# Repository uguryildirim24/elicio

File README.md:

# Elicio

Elicio is an unfinished ear-muscle EMG earpiece that is intended to turn a deliberate contraction into a gated event before an AI acts.

Rolf chose a discreet physical input rather than an always-active command channel. The sensor should propose an event. Policy should decide whether that event can act. Sensing, permission and execution remain separate.

```text
ear-muscle EMG -> decoder -> (symbol, confidence, timestamp) -> policy -> action
```

**The board is not finished, has not been ordered and is unmeasured.** No physical earpiece, real ear-muscle recording or end-to-end biological action has been validated. The runnable demonstrations use synthetic input. Only a harmless local file action is real. No AI execution adapter is implemented.

## What exists

| Part | Files and present evidence |
| --- | --- |
| Flex board | [KiCad schematic](hardware/board/elicio-v4.kicad_sch), [routed PCB](hardware/board/elicio-v4.kicad_pcb), project rules and generation/routing scripts. Design files are not manufacturing approval. |
| Scripted shell | [Selected snap-shell exports](docs/fab/cad/v4-snap/) include STEP, STL, 3MF and a nominal-check manifest. No print, fit or retention result. |
| Firmware | [Arduino stream firmware](firmware/elicio_stream/elicio_stream.ino) and C sources for ADS1292 acquisition, binary BLE frames and undervoltage handling. The product Arduino variant is missing. |
| Receiver | Binary frame decoding, dropout/loss records and session files. Committed synthetic transport fixtures run without a radio. |
| Action gate | Confidence policy, confirmation state, intent/result auditing and an atomic local marker write. Other action names are console simulations. |
| Research pipeline | Public forearm sEMG preparation and cross-session evaluation code. No result CSVs, checkpoints or measured accuracy reports are bundled. |

The snap manifest records **106 passing nominal geometry checks**. These cover simplified board courtyards, a folded-flap envelope, seated overlap, key clearance and opposing tolerance offsets. They do not prove printed fit, latch fatigue, component loads, electrical safety or RF range. The nominal body is 18 mm wide and 8.1 mm thick, not the complete hook bounding box. See [shell limits](docs/fab/shell-v4.md) and [board blockers](docs/fab/board-v4-design.md).

## Run from a clean clone

Run these commands from the repository root on macOS or Linux. Use Python **3.11 or newer**. The base install requires NumPy. No credentials or hardware are needed for the demos.

```bash
python3 --version
python3 -m venv .venv
.venv/bin/python -m pip install -e .
.venv/bin/elicio demo --state-dir .elicio-demo
.venv/bin/elicio replay-demo --state-dir .elicio-replay-demo
```

Each demo must exit 0 and print `"verified": true`. It writes a marker under `actions/` and linked `intent` and `result` records in `audit.jsonl` inside its ignored state directory. The replay fixture is seeded synthetic data, not an EMG recording or a hardware test.

### Binary receiver without hardware

```bash
.venv/bin/elicio receive --simulate tests/fixtures/receiver_v2/normal.json \
    --out recordings/synthetic-session
.venv/bin/elicio receive-check recordings/synthetic-session
```

`receive` writes `samples.npz`, `sidecar.json` and `meta.json`. `receive-check` reports acquisition statistics and criterion status; the normal fixture exits 0 with `"ok": true`. Its gesture criteria are `not_scored`, not passed. This is transport validation, not gesture decoding or a connection to the action gate.

The intended radio path uses binary frame-v2 messages over Nordic UART Service, not ASCII serial samples. Live reception requires the optional BLE dependency and future functioning hardware:

```bash
.venv/bin/python -m pip install -e '.[ble]'
.venv/bin/elicio receive --device ELICIO --seconds 10 --out recordings/bench-session
.venv/bin/elicio receive-check recordings/bench-session
```

The live commands are not usable or validated with this unfinished board. The firmware deliberately rejects a Feather pin variant. See [firmware limits](docs/fab/firmware-v2.md), [frame format](docs/fab/frame-v2.md) and [receiver contract](docs/fab/receiver-v2.md).

The separate `scope`, `capture` and `replay-recording` tools accept one ASCII sample per line from a file, stdin or an already configured serial device. They are bench utilities, not the binary BLE path. Store captures under ignored `recordings/`, for example `--out recordings/session.json`. Run `elicio capture --help` for the sample-rate, offset and gain arguments.

### Existing tests

```bash
.venv/bin/python -m unittest discover -s tests -v
```

The scope review ran the base install, both synthetic action demos and the normal receiver fixture in the worktree with Python 3.13.15. They exited 0. Both demos reported `verified: true`; the receiver check reported `ok: true` with gesture criteria unscored.

The full existing suite was attempted but stopped at a 180-second command limit while setting up the restored packing checks. A historical document wording assertion failed before that point. Its expected reference wording was restored, and that existing test passed when rerun alone. The documented `bte_fit_shell.py --checks-only` reference check and `elicio capture --help` also passed. No complete suite pass is claimed. The original tests and historical-byte comparisons remain unchanged. No tests or CI were added.

Optional dependency groups are `research`, `ble`, `cad` and `sheets`. Install an extra with, for example, `.venv/bin/python -m pip install -e '.[cad]'`. Native C checks use a compiler when available. KiCad/pcbnew, firmware tooling, Blender or SceneKit are separate toolchains. Optional CAD exports, rendering, KiCad release validation, firmware flashing and live acquisition were not rerun during the scope review. Research downloads and training were skipped as substantial workloads.

## Research and local data

The research package fetches public PhysioNet/WFDB GRABMyo records. It studies forearm gestures, not auricular decoding. From the repository root:

```bash
.venv/bin/python -m pip install -e '.[research]'
.venv/bin/elicio-emg prepare --subjects 1 2 3 --out-dir results
.venv/bin/elicio-emg train --data-dir results --subjects 1 2 3 \
    --epochs 20 --out results/train_results.csv
.venv/bin/elicio-emg evaluate --data-dir results --subjects 1 2 3 \
    --epochs 20 --out results/six_best_rest.csv
```

These are download and training workloads, not quick demos. They were not rerun during cleanup. Training is not fully seeded. Evaluation uses separate recording sessions and a leakage guard. Earlier imported accuracy summaries lack supporting result artifacts here and are not claimed as repository results. See the [pipeline instructions](src/elicio/pipeline/README.md) and [provenance limits](docs/RESEARCH_PROVENANCE.md).

Keep raw recordings in `recordings/`, research outputs in `results/`, anatomy parameters in `measurements/` and generated CAD/release output in `.reports/`. These directories, environments, checkpoints, secrets and runtime state are ignored. Tracked binary fixtures are synthetic. No completed personal ear measurements or purchase records are included. Do not put delivery addresses, checkout details or credentials in public examples.

## Limits and next steps

- Confidence thresholds are policy settings, not calibrated biological probabilities.
- The timed `jaw_clench` confirmation rule checks symbols, confidence and timestamps. The event tuple cannot prove that command and confirmation came from independent muscle groups. That is an unvalidated upstream requirement.
- Intent audit failure blocks execution. A result-audit failure after execution is reported without hiding the completed action.
- There is no trained ear-muscle decoder, real signal-to-action result or AI execution adapter.
- The circuit, cell, charging protection, RF keep-out, programming path and manufacturing acceptance remain open. CAD and a clean DRC claim cannot establish on-body safety.
- This is not a medical device or a finished wearable. Do not wear or charge unvalidated electronics on a body.

Next: resolve electrical and fabrication blockers, implement the product firmware variant, validate passive printed fit and repeated latch retention, then record a real signal and demonstrate one harmless audited action. See [design status](docs/EARPIECE_DESIGN.md) and [open gates](docs/fab/open-questions.md).

## Project layout

| Path | Purpose |
| --- | --- |
| `src/elicio/harness/` | Events, policy, adapters and audit |
| `src/elicio/signal/` | Synthetic replay, detection and ASCII capture |
| `src/elicio/frame_v2.py`, `receiver_v2.py` | Binary BLE transport and session reception |
| `src/elicio/pipeline/` | Public-data research pipeline |
| `hardware/board/` | KiCad sources, custom footprints and board scripts |
| `firmware/` | Acquisition, framing and power-state sources |
| `scripts/cad/`, `scripts/sheets/` | Parametric CAD, previews and reference templates |
| `docs/fab/cad/v4-snap/` | Selected shell candidate and nominal evidence |
| `tests/` | Existing unit checks and synthetic transport fixtures |
| `docs/` | Design limits, provenance and engineering references |

Older v1/v2 geometry, packing tables, layout searches, board-edit scripts and their existing checks remain. They are reference inputs and development tools, not active ordering instructions. `placement.py` still supports `--packing-doc`, `--layout-v2` and `--layout-v2c`. Some older readers use pinned Git revisions. They are not independent of repository history, and history scrubbing can invalidate those references. The technical L1 to L8 source surveys remain with historical notices. The [reference index](docs/fab/references.md) lists key public sources. Task and review dialogue is omitted.

The rejected M1.6 closure remains as diagnostic code and evidence in `docs/fab/cad/v4-m16/`. It is not suitable for printing. The snap candidate is still untested physically. Private agent diaries, personal parameter scaffolding and superseded shopping sheets were removed. Historical budgets are estimates, not quotes or personal spending statements.

## How this was built

AI coding agents did much of the research migration, harness and receiver implementation, firmware, CAD and board work under Rolf's direction. Rolf set the physical-gating goal, chose the earpiece form, titanium contacts, limited final assembly and off-ear-only charging, and reviewed design previews. The checks reported here are automated software and nominal geometry checks. Agent-written engineering claims are not independent electrical review or physical measurements. No hardware result has been measured.

## License and citation

Original project code, hardware design files and documentation are offered under [MIT](LICENSE). The bundled Liberation Sans font is separate: SIL Open Font License 1.1, with Google and Red Hat attribution in [the font notice](scripts/cad/fonts/OFL.txt). External datasets, dependencies and vendor materials retain their own terms.

No Elicio paper or preprint is included in this repository. Public engineering source pointers are in [references](docs/fab/references.md).

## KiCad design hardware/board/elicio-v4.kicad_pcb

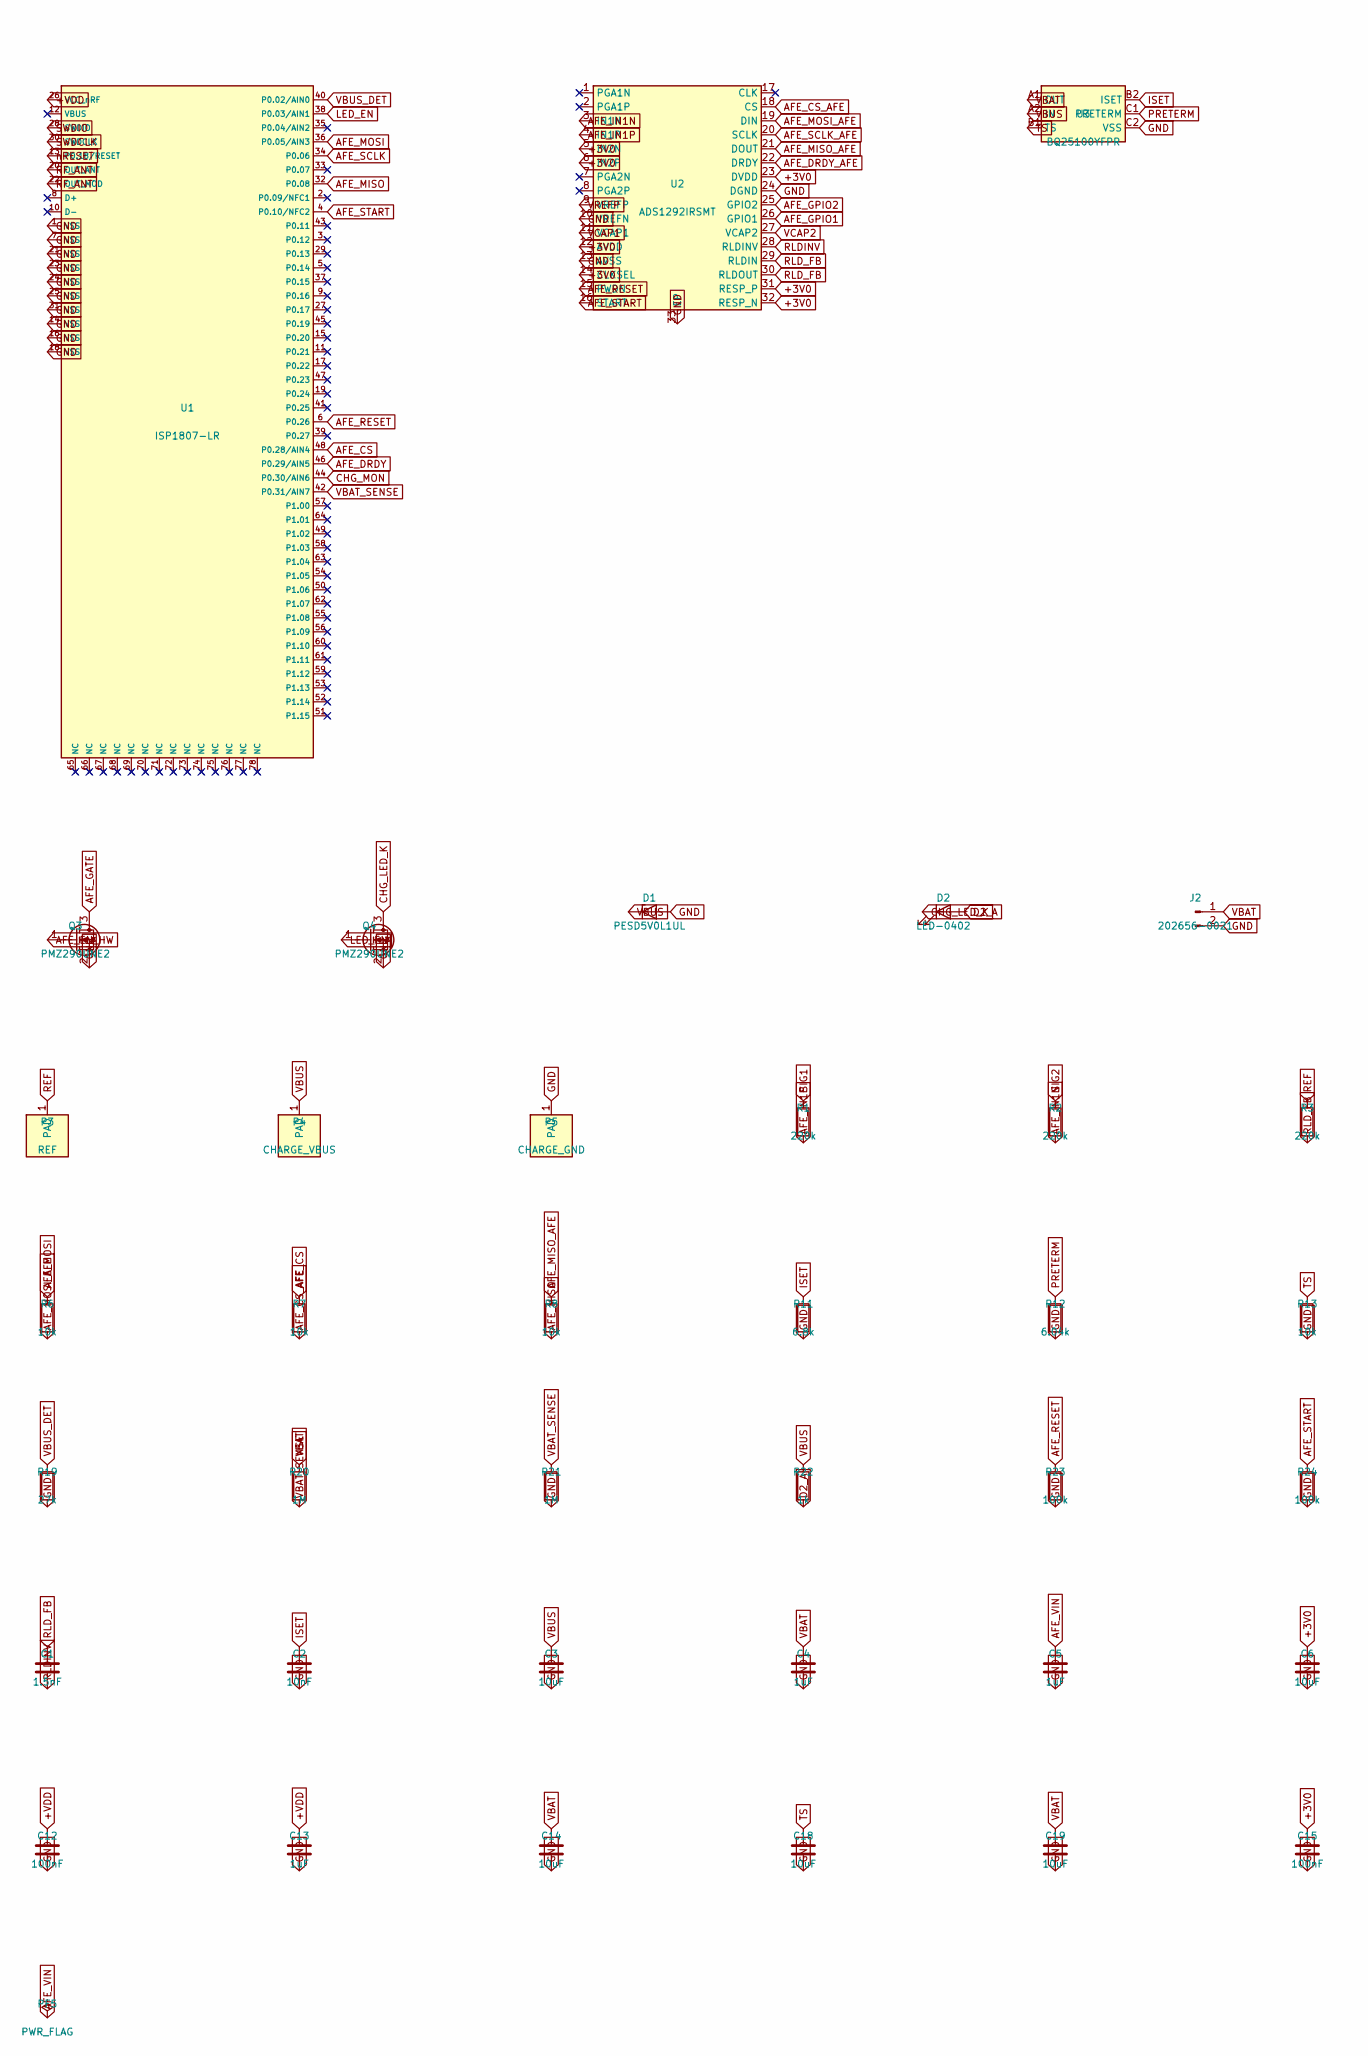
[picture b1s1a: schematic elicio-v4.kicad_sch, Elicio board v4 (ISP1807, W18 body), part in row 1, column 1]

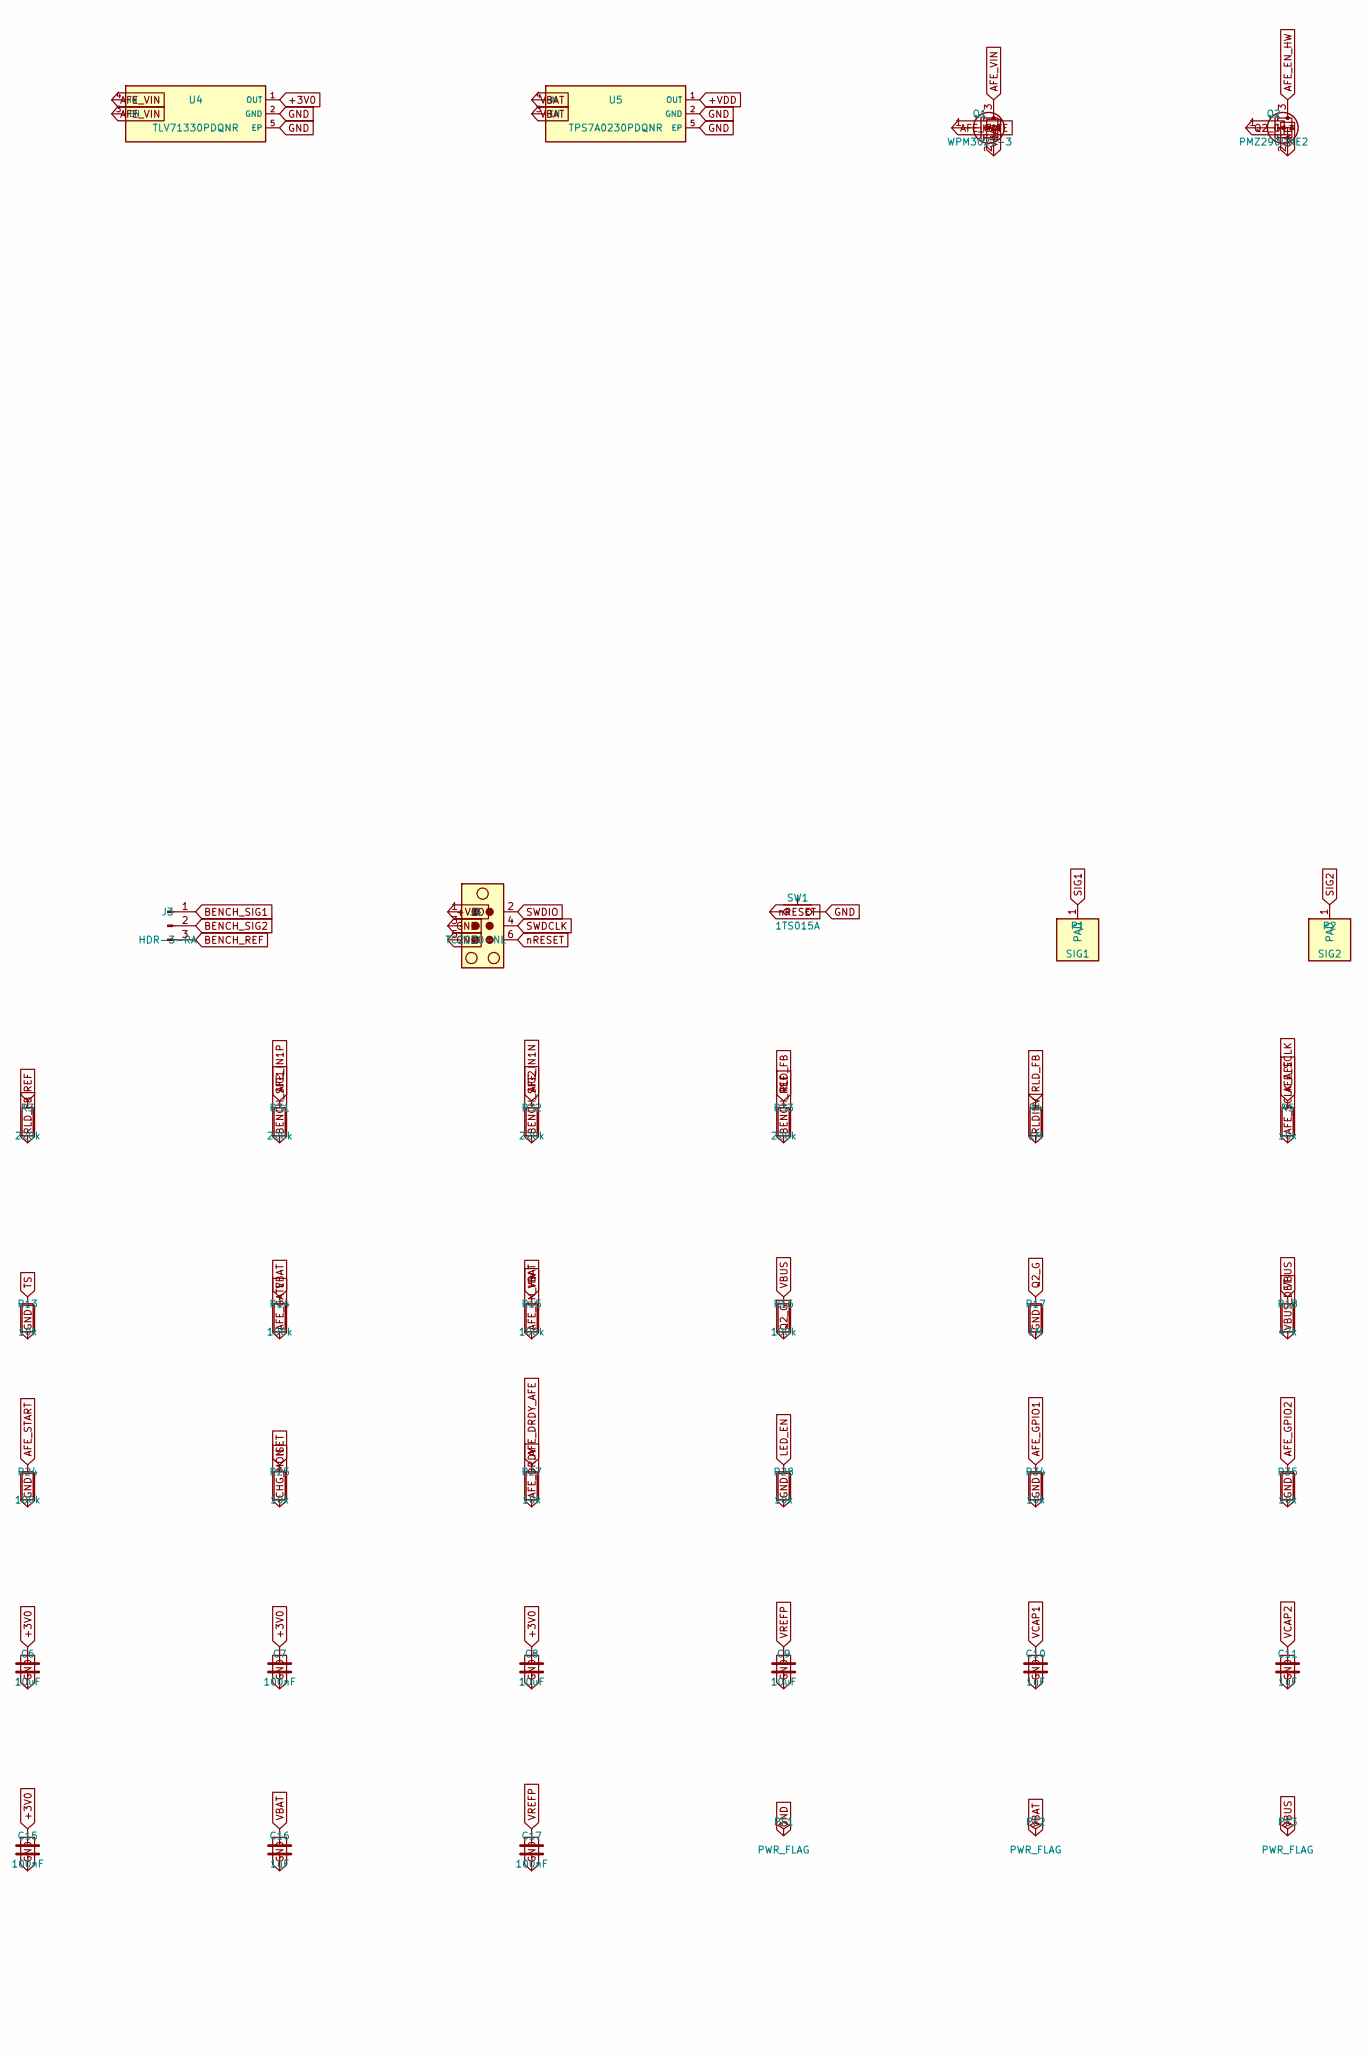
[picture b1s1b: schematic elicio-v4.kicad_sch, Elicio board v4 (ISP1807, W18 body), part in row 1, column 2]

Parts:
C1: 1.5nF; C_0201_0603Metric; MPN 0201B152K500NT; LCSC C285104
C2: 10nF; C_0201_0603Metric; MPN TCC0201X7R103K500ZT; LCSC C5142551
C3, C14, C18, C19: 10uF; C_0402_1005Metric; MPN GRM155R61A106ME18D; LCSC C36626211
C4, C5, C10, C11, C13, C16: 1uF; C_0201_0603Metric; MPN TCC0201X5R105K6R3ZT; LCSC C5142566
C6, C8, C9: 10uF; C_0402_1005Metric; MPN CL05A106MQ5NUNC; LCSC C15525
C7, C12, C15, C17: 100nF; C_0201_0603Metric; MPN CL03A104KO3NNNC; LCSC C307380
D1: PESD5V0L1UL; D_SOD-882; MPN PESD5V0L1UL; LCSC C3001948
D2: LED-0402; LED_0402_1005Metric; MPN LTST-C281TGKT-5A; LCSC C364549
J2: 202656-0021; Molex_Pico-EZmate_Slim_202656-0021_1x02-1MP_P1.20mm_Vertical; MPN 202656-0021; LCSC CONSIGNED
J3: HDR-3-RA; PinHeader_1x03_P2.54mm_Horizontal; LCSC C49257
J4: TC2030-NL; Tag-Connect_TC2030-IDC-NL_2x03_P1.27mm_Vertical
P1: SIG1; RING_PAD_D5_H2.7
P2: SIG2; RING_PAD_D5_H2.7
P3: REF; RING_PAD_D5_H2.7
P4: CHARGE_VBUS; RING_1S_D4.6_NPTH2.7
P5: CHARGE_GND; RING_1S_D4.6_NPTH2.7
PF1, PF2, PF3, PF5: PWR_FLAG
Q1: WPM3027-3; SOT-883; MPN WPM3027-3/TR; LCSC C240195
Q2, Q3, Q4: PMZ290UNE2; SOT-883; MPN PMZ290UNE2YL; LCSC C478155
R1, R2, R3, R31, R32, R33: 220k; R_0402_1005Metric; LCSC C881401
R4, R17, R20, R21: 1M; R_0201_0603Metric; MPN 0201WMF1004TEE; LCSC C473482
R5, R6, R7, R8, R13, R25, R27, R28, R34, R35: 10k; R_0201_0603Metric; MPN 0201WMF1002TEE; LCSC C473048
R11: 6.8k; R_0201_0603Metric; MPN 0201WMF6801TEE; LCSC C423451
R12: 6.04k; R_0201_0603Metric; MPN 0201WMF6041TEE; LCSC C270341
R14, R15, R16, R23, R24: 100k; R_0201_0603Metric; MPN 0201WMF1003TEE; LCSC C270364
R18: 47k; R_0201_0603Metric; LCSC C270345
R19: 27k; R_0201_0603Metric; LCSC C270351
R22: 1k; R_0201_0603Metric; MPN 0201WMF1001TEE; LCSC C270365
SW1: 1TS015A; SW_HRO_1TS015A; MPN 1TS015A-1200-0600-CT; LCSC C398746
U1: ISP1807-LR; InsightSiP_ISP1807; MPN ISP1807-LR-RS; LCSC CONSIGNED
U2: ADS1292IRSMT; Texas_RSM0032; MPN ADS1292IRSMT; LCSC C89288
U3: BQ25100YFPR; Texas_YFP0006_V4; MPN BQ25100YFPR; LCSC CONSIGNED
U4: TLV71330PDQNR; Texas_X2SON-4_1x1mm_P0.65mm; MPN TLV71330PDQNR; LCSC C2863576
U5: TPS7A0230PDQNR; Texas_X2SON-4_1x1mm_P0.65mm; MPN TPS7A0230PDQNR; LCSC C2867950

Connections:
+3V0: C6.1, C7.1, C8.1, C15.1, U2.5 (IN2N), U2.6 (IN2P), U2.12 (AVDD), U2.14 (CLKSEL), U2.23 (DVDD), U2.31 (RESP_P), U2.32 (RESP_N), U4.1 (OUT)
+VDD: C12.1, C13.1, J4.1, U1.26 (VCC_nRF), U5.1 (OUT)
AFE_CS: R7.1, U1.48 (P0.28/AIN4)
AFE_CS_AFE: R7.2, U2.18 (CS)
AFE_DRDY: R27.2, U1.46 (P0.29/AIN5)
AFE_DRDY_AFE: R27.1, U2.22 (DRDY)
AFE_EN_HW: Q2.3 (D), Q3.1 (G), R15.2
AFE_GATE: Q1.1 (G), Q3.3 (D), R14.2
AFE_GPIO1: R34.1, U2.26 (GPIO1)
AFE_GPIO2: R35.1, U2.25 (GPIO2)
AFE_IN1N: R2.2, R32.1, U2.3 (IN1N)
AFE_IN1P: R1.2, R31.1, U2.4 (IN1P)
AFE_MISO: R8.2, U1.32 (P0.08)
AFE_MISO_AFE: R8.1, U2.21 (DOUT)
AFE_MOSI: R6.1, U1.36 (P0.05/AIN3)
AFE_MOSI_AFE: R6.2, U2.19 (DIN)
AFE_RESET: R23.1, U1.6 (P0.26), U2.15 (PWDN)
AFE_SCLK: R5.1, U1.34 (P0.06)
AFE_SCLK_AFE: R5.2, U2.20 (SCLK)
AFE_START: R24.1, U1.4 (P0.10/NFC2), U2.16 (START)
AFE_VIN: C5.1, PF5.1, Q1.3 (D), U4.3 (EN), U4.4 (IN)
BENCH_REF: J3.3, R33.2
BENCH_SIG1: J3.1, R31.2
BENCH_SIG2: J3.2, R32.2
CHG_LED_K: D2.1 (K), Q4.3 (D)
CHG_MON: R25.2, U1.44 (P0.30/AIN6)
D2_A: D2.2 (A), R22.2
GND: C2.2, C3.2, C4.2, C5.2, C6.2, C7.2, C8.2, C9.2, C10.2, C11.2, C12.2, C13.2, C14.2, C15.2, C16.2, C17.2, C18.2, C19.2, D1.2 (A), J2.2, J2.MP, J4.3, J4.5, P5.1, PF1.1, Q2.2 (S), Q3.2 (S), Q4.2 (S), R11.2, R12.2, R13.2, R17.2, R19.2, R21.2, R23.2, R24.2, R28.2, R34.2, R35.2, SW1.2, U1.1 (VSS), U1.7 (VSS), U1.14 (VSS), U1.16 (VSS), U1.18 (VSS), U1.21 (VSS), U1.23 (VSS), U1.24 (VSS), U1.25 (VSS), U1.31 (VSS), U2.10 (VREFN), U2.13 (AVSS), U2.24 (DGND), U2.33 (EP), U3.C2 (VSS), U4.2 (GND), U4.5 (EP), U5.2 (GND), U5.5 (EP)
ISET: C2.1, R11.1, R25.1, U3.B2 (ISET)
LED_EN: Q4.1 (G), R28.1, U1.38 (P0.03/AIN1)
PRETERM: R12.1, U3.C1 (PRETERM)
Q2_G: Q2.1 (G), R16.2, R17.1
REF: P3.1, R3.1
RF_ANT: U1.20 (OUT_ANT), U1.22 (OUT_MOD)
RLDINV: C1.2, R4.2, U2.28 (RLDINV)
RLD_FB: C1.1, R3.2, R4.1, R33.1, U2.29 (RLDIN), U2.30 (RLDOUT)
SIG1: P1.1, R1.1
SIG2: P2.1, R2.1
SWDCLK: J4.4, U1.30 (SWDCLK)
SWDIO: J4.2, U1.28 (SWDIO)
TS: C18.1, R13.1, U3.B1 (TS)
VBAT: C4.1, C14.1, C16.1, C19.1, J2.1, PF2.1, Q1.2 (S), R14.1, R15.1, R20.1, U3.A1 (OUT), U5.3 (EN), U5.4 (IN)
VBAT_SENSE: R20.2, R21.1, U1.42 (P0.31/AIN7)
VBUS: C3.1, D1.1 (K), P4.1, PF3.1, R16.1, R18.1, R22.1, U3.A2 (IN)
VBUS_DET: R18.2, R19.1, U1.40 (P0.02/AIN0)
VCAP1: C10.1, U2.11 (VCAP1)
VCAP2: C11.1, U2.27 (VCAP2)
VREFP: C9.1, C17.1, U2.9 (VREFP)
nRESET: J4.6, SW1.1, U1.13 (P0.18/RESET)

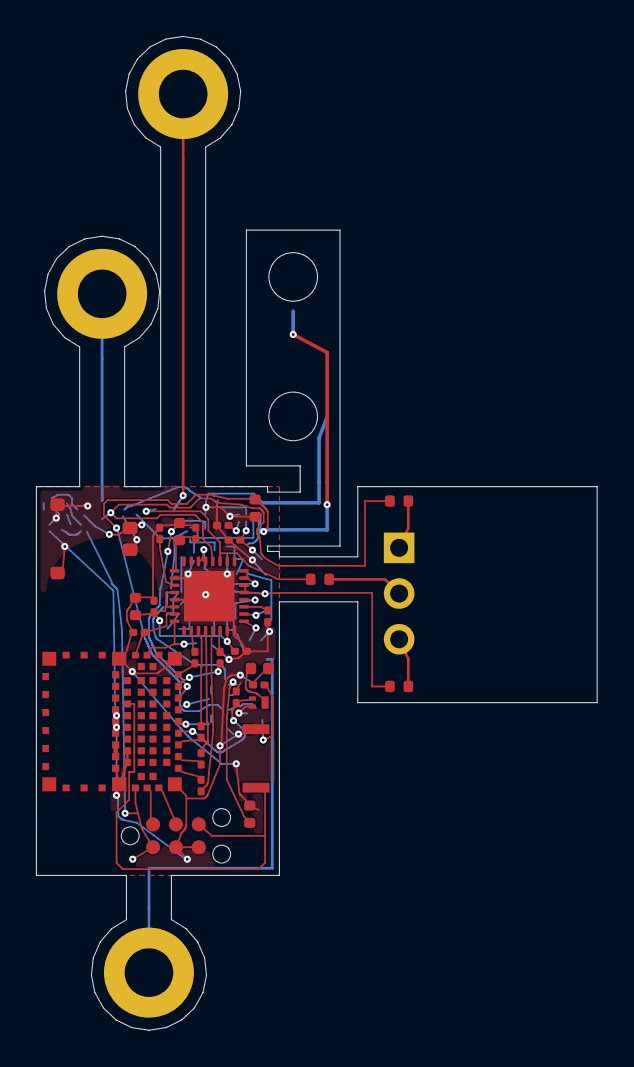
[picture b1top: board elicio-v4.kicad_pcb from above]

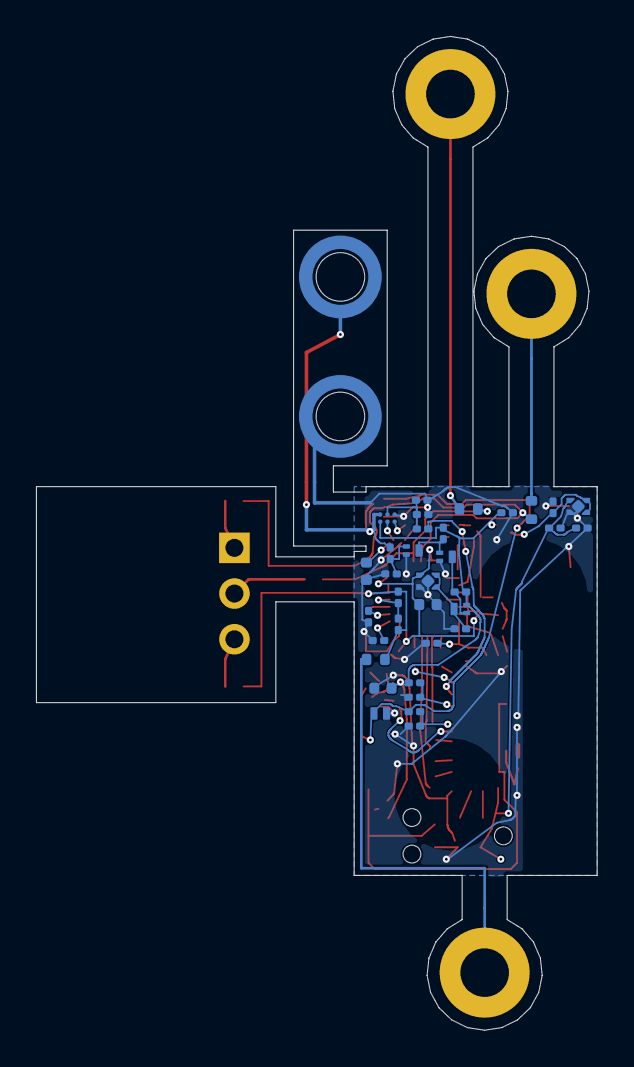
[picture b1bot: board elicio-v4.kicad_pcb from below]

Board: 2 copper layers, 31.1 x 55.2 mm, 69 parts (36 on the bottom side), 49 nets.

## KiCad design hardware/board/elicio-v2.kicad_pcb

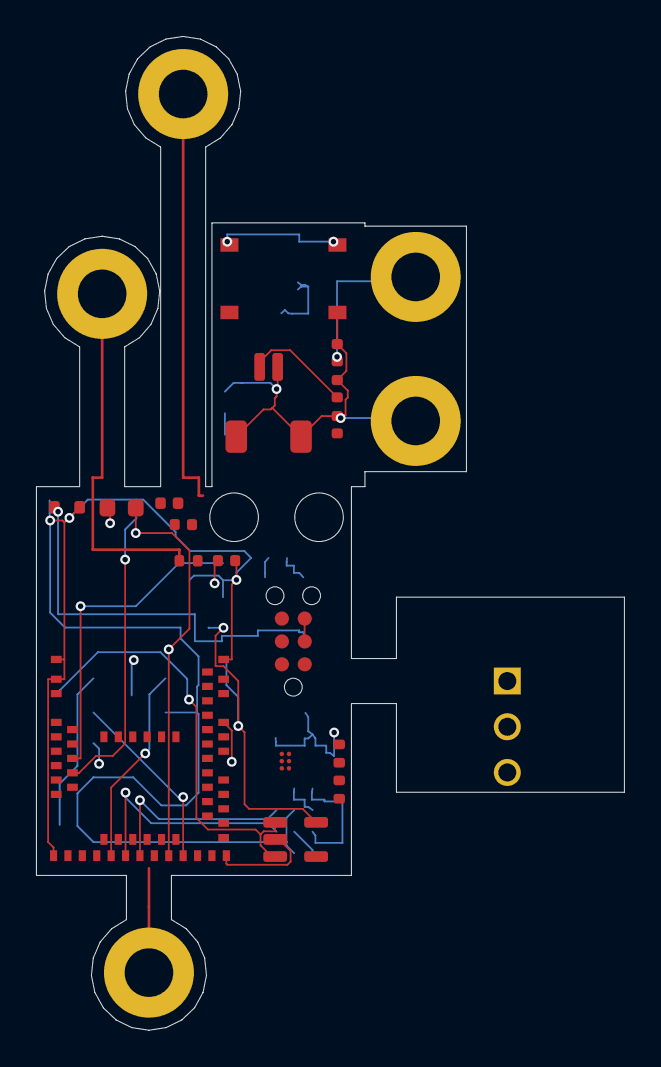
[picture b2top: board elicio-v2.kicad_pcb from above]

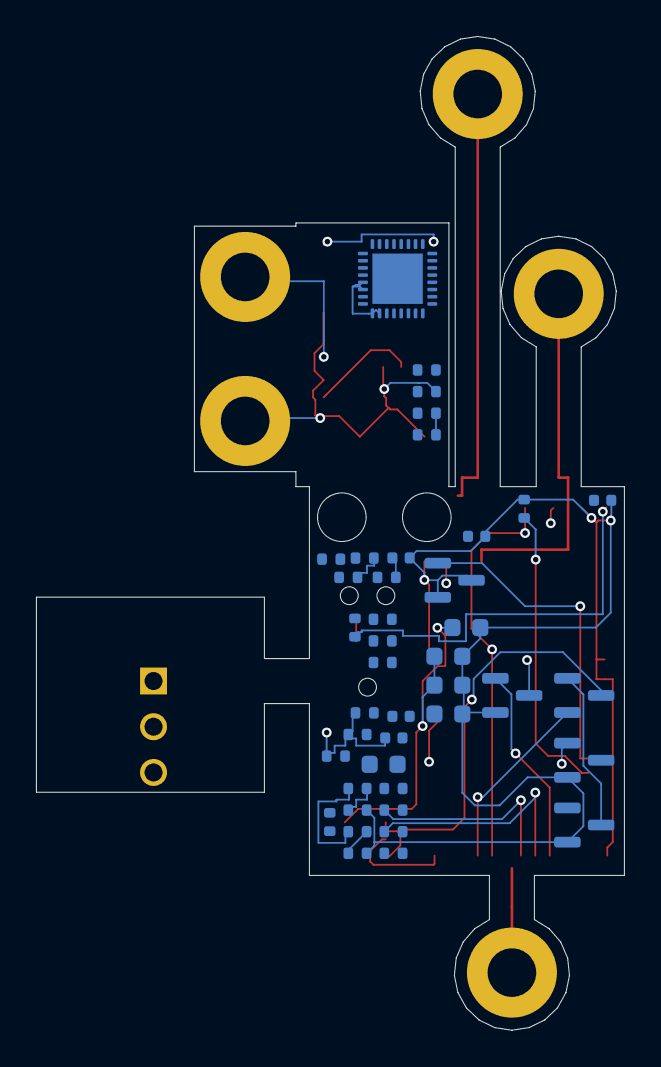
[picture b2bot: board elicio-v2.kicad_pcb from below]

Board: 2 copper layers, 32.7 x 55.2 mm, 66 parts (41 on the bottom side), 45 nets.

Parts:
C1: 1.5nF; C_0402_1005Metric
C2: 10nF; C_0402_1005Metric
C3, C4, C5, C10, C13: 1uF; C_0402_1005Metric
C6, C8, C9: 10uF; C_0603_1608Metric
C7, C15: 100nF; C_0603_1608Metric
C11, C12: 100nF; C_0402_1005Metric
C14: 4.7uF; C_0402_1005Metric
D1: PESD5V0L1UL; D_SOD-523
D2: LED-0402; LED_0402_1005Metric
H1, H2: HOLE_D2.7; MountingHole_M2.5
J2: SM02B-SRSS-TB; JST_SH_SM02B-SRSS-TB_1x02-1MP_P1.00mm_Horizontal
J3: HDR-3-RA; PinHeader_1x03_P2.54mm_Horizontal
J4: TC2030-NL; Tag-Connect_TC2030-IDC-NL_2x03_P1.27mm_Vertical
L1: 10uH; L_0603_1608Metric
P1: SIG1; RING_PAD_D5_H2.7
P2: SIG2; RING_PAD_D5_H2.7
P3: REF; RING_PAD_D5_H2.7
P4: CHARGE_VBUS; RING_PAD_D5_H2.7
P5: CHARGE_GND; RING_PAD_D5_H2.7
Q1: AO3401A; SOT-23
Q2, Q3, Q4, Q5: 2N7002; SOT-23
R1, R2, R3: 220k; R_0402_1005Metric
R4, R17, R20, R21: 1M; R_0402_1005Metric
R5, R6, R7, R8, R13, R25, R26, R27, R28: 10k; R_0402_1005Metric
R11: 6.80k; R_0402_1005Metric
R12: 6.04k; R_0402_1005Metric
R14, R15, R16, R23, R24: 100k; R_0402_1005Metric
R18: 47k; R_0402_1005Metric
R19: 27k; R_0402_1005Metric
R22: 1k; R_0402_1005Metric
R29, R30: 10M; R_0402_1005Metric
SW1: 4.5x4.5x1.6; SW_Push_1P1T_XKB_TS-1187A
U1: MDBT50Q-1MV2; Raytac_MDBT50Q
U2: ADS1292IRSMT; Texas_RSM0032
U3: BQ25100YFPR; Texas_YFP0006
U4: TLV71330PDBVR; SOT-23-5

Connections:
+3V0: C6.1, C7.1, C8.1, C15.1, U2.5, U2.6, U2.12, U2.14, U2.23, U2.31, U2.32, U4.5
+VDD: C12.1, C13.1, J4.1, L1.2, R26.2, U1.28
AFE_CS: R7.1, U1.37
AFE_CS_AFE: R7.2, U2.18
AFE_DRDY: R27.2, U1.41
AFE_DRDY_AFE: R27.1, U2.22
AFE_EN_HW: Q2.3, Q3.1, R15.2
AFE_GATE: Q1.1, Q3.3, R14.2
AFE_IN1N: R2.2, R30.1, U2.3
AFE_IN1P: R1.2, R29.1, U2.4
AFE_MISO: R8.2, U1.39
AFE_MISO_AFE: R8.1, U2.21
AFE_MOSI: R6.1, U1.22
AFE_MOSI_AFE: R6.2, U2.19
AFE_RESET: R23.1, U1.46, U2.15
AFE_SCLK: R5.1, U1.24
AFE_SCLK_AFE: R5.2, U2.20
AFE_START: R24.1, U1.44, U2.16
AFE_VIN: C5.1, Q1.3, U4.1, U4.3
BAT_MEAS_EN: Q5.1, U1.9
CHG_LED_K: D2.1, Q4.3
CHG_MON: R25.2, U1.12
D2_A: D2.2, R22.2
DCCH: L1.1, U1.31
GND: C2.2, C3.2, C4.2, C5.2, C6.2, C7.2, C8.2, C9.2, C10.2, C11.2, C12.2, C13.2, C14.2, C15.2, D1.2, J2.2, J2.MP, J4.3, J4.5, P5.1, Q2.2, Q3.2, Q4.2, Q5.2, Q5.3, R11.2, R12.2, R13.2, R17.2, R19.2, R21.2, R23.2, R24.2, R28.2, SW1.2, U1.1, U1.2, U1.15, U1.33, U1.55, U2.10, U2.13, U2.24, U2.33, U3.C2, U4.2
ISET: C2.1, R11.1, R25.1, U3.B2
LED_EN: Q4.1, R28.1, U1.20
PRETERM: R12.1, U3.C1
Q2_G: Q2.1, R16.2, R17.1
REF: J3.3, P3.1, R3.1
RLDINV: C1.2, R4.2, U2.28
RLD_FB: C1.1, R3.2, R4.1, R29.2, R30.2, U2.29, U2.30
SIG1: J3.1, P1.1, R1.1
SIG2: J3.2, P2.1, R2.1
SWDCLK: J4.4, U1.53
SWDIO: J4.2, U1.51
TS: R13.1, U3.B1
VBAT: C4.1, C14.1, J2.1, Q1.2, R14.1, R15.1, R20.1, U1.30, U3.A1
VBAT_SENSE: R20.2, R21.1, U1.11
VBUS: C3.1, D1.1, P4.1, R16.1, R18.1, R22.1, U1.32, U3.A2
VBUS_DET: R18.2, R19.1, U1.48
VCAP1: C10.1, U2.11
VCAP2: C11.1, U2.27
VREFP: C9.1, U2.9
nRESET: J4.6, R26.1, SW1.1, U1.40

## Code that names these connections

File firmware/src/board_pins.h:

#ifndef ELICIO_BOARD_PINS_H
#define ELICIO_BOARD_PINS_H

/*
 * v4 ISP1807-LR pad -> nRF52840 P0.xx (not Feather digital pin numbers).
 * Source: ISP1807 datasheet R19 §3 pin table, pp. 10-11,
 * https://www.insightsip.com/fichiers_insightsip/pdf/ble/ISP1807/isp_ble_DS1807.pdf
 * read 2026-09-25; net assignments: committed elicio-v4.kicad_sch/pcb.
 * A product Arduino variant must map these physical pins to its digital pins;
 * the Feather SPI object and digital-pin indices are NOT the product variant.
 */
#define ELICIO_PIN_ADS_SCLK 6 /* P0.06, U1.34 AFE_SCLK */
#define ELICIO_PIN_ADS_MOSI 5 /* P0.05, U1.36 AFE_MOSI */
#define ELICIO_PIN_ADS_MISO 8 /* P0.08, U1.32 AFE_MISO */
#define ELICIO_PIN_ADS_CS 28 /* P0.28, U1.48 AFE_CS; LF only */
#define ELICIO_PIN_ADS_DRDY 29 /* P0.29, U1.46 AFE_DRDY; LF only */
#define ELICIO_PIN_ADS_START 10 /* P0.10, U1.4 AFE_START; NFC2 as GPIO */
#define ELICIO_PIN_ADS_PWDN 26 /* P0.26, U1.6 AFE_RESET (ADS PWDN/RESET) */
#define ELICIO_PIN_VBUS_DET 2 /* P0.02, U1.40 VBUS_DET; LF only */
#define ELICIO_PIN_CHG_MON 30 /* P0.30, U1.44 CHG_MON; AIN6, LF only */
#define ELICIO_PIN_VBAT_SENSE 31 /* P0.31, U1.42 VBAT_SENSE; AIN7, LF only */
#define ELICIO_PIN_LED_EN 3 /* P0.03, U1.38 LED_EN; LF only */
#define ELICIO_PIN_NRESET 18 /* P0.18, U1.13 nRESET; configure UICR PSELRESET */

/* U1.28 SWDIO and U1.30 SWDCLK are dedicated debug signals, not GPIO.
 * U1.26 +VDD comes from U5; U1.20/22 RF_ANT, VSS pads 1,7,14,16,18,
 * 21,23,24,25,31. U1.8/10 USB and U1.12 VBUS are not connected.
 * BAT_MEAS_EN / Q5 were removed; AFE_EN_HW is a hardware charge interlock,
 * not MCU GPIO. Charge status is the ADC CHG_MON net (no separate STAT pin).
 */
#endif

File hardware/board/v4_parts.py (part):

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    "32": "AFE_MISO",  # P0.08 (input)
    # -s edge, facing U2's west pads 15/16.
    "6": "AFE_RESET",  # P0.26
    "4": "AFE_START",  # P0.10/NFC2 (NFCT pins as GPIO; pad 2 NFC1 left open)
}


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                "13": "GND", "14": "+3V0", "15": "AFE_RESET", "16": "AFE_START", "17": None,
                "18": "AFE_CS_AFE", "19": "AFE_MOSI_AFE", "20": "AFE_SCLK_AFE",
                "21": "AFE_MISO_AFE", "22": "AFE_DRDY_AFE", "23": "+3V0", "24": "GND",
                "25": "AFE_GPIO2", "26": "AFE_GPIO1", "27": "VCAP2", "28": "RLDINV", "29": "RLD_FB",
                "30": "RLD_FB", "31": "+3V0", "32": "+3V0", "33": "GND",
            },
            lcsc="C89288", mpn="ADS1292IRSMT",
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             "Connector_PinHeader_2.54mm:PinHeader_1x03_P2.54mm_Horizontal",
             # Bench nets: each pin has its own 220 kOhm (R31-R33) on the tab
             # side of the cut, so no Contact copper crosses the cut (§5.4, Q97).
             # Pin 1 SIG1 side, 2 SIG2 side, 3 REF side (v2's order): the
             # AFE inputs enter the island north of RLD_FB, as U2's pads sit.
             {"1": "BENCH_SIG1", "2": "BENCH_SIG2", "3": "BENCH_REF"}, lcsc="C49257"),
        Part("J4", "Connector:TC2030", "TC2030-NL",
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        r("R25", "10k", "ISET", "CHG_MON"),
        r("R27", "10k", "AFE_DRDY_AFE", "AFE_DRDY"),
        r("R28", "10k", "LED_EN", "GND"),
        # ADS1292 GPIO1/GPIO2 default to inputs and must not float (SBAS502C §8.5.1.7).
        r("R34", "10k", "AFE_GPIO1", "GND"),
        r("R35", "10k", "AFE_GPIO2", "GND"),
        c("C1", "1.5nF", "RLD_FB", "RLDINV"),
        c("C2", "10nF", "ISET", "GND"),
        esd_cap("C3", "10uF", "VBUS", "GRM155R61A106ME18"),
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        c("C8", "10uF", "+3V0", "GND", "0402"),
        c("C9", "10uF", "VREFP", "GND", "0402"),
        c("C10", "1uF", "VCAP1", "GND"),
        c("C11", "1uF", "VCAP2", "GND"),  # 1 uF at pin 27 (SBAS502C Fig. 73)
        c("C12", "100nF", "+VDD", "GND"),
        c("C13", "1uF", "+VDD", "GND"),
        esd_cap("C14", "10uF", "VBAT", "GRM155R61A106ME18"),
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        c("C16", "1uF", "VBAT", "GND"),
        c("C17", "100nF", "VREFP", "GND"),  # local VREFP bypass beside C9 (SBAS502C Fig. 73)
    ]
    flags = [("PF1", "GND"), ("PF2", "VBAT"), ("PF3", "VBUS"), ("PF5", "AFE_VIN")]
    out += [
        Part(ref, "power:PWR_FLAG", "PWR_FLAG", "", {"1": net}, in_bom=False, on_board=False)
        for ref, net in flags
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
